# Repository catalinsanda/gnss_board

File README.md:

# gnss_board
Hardware design for the GNSS project

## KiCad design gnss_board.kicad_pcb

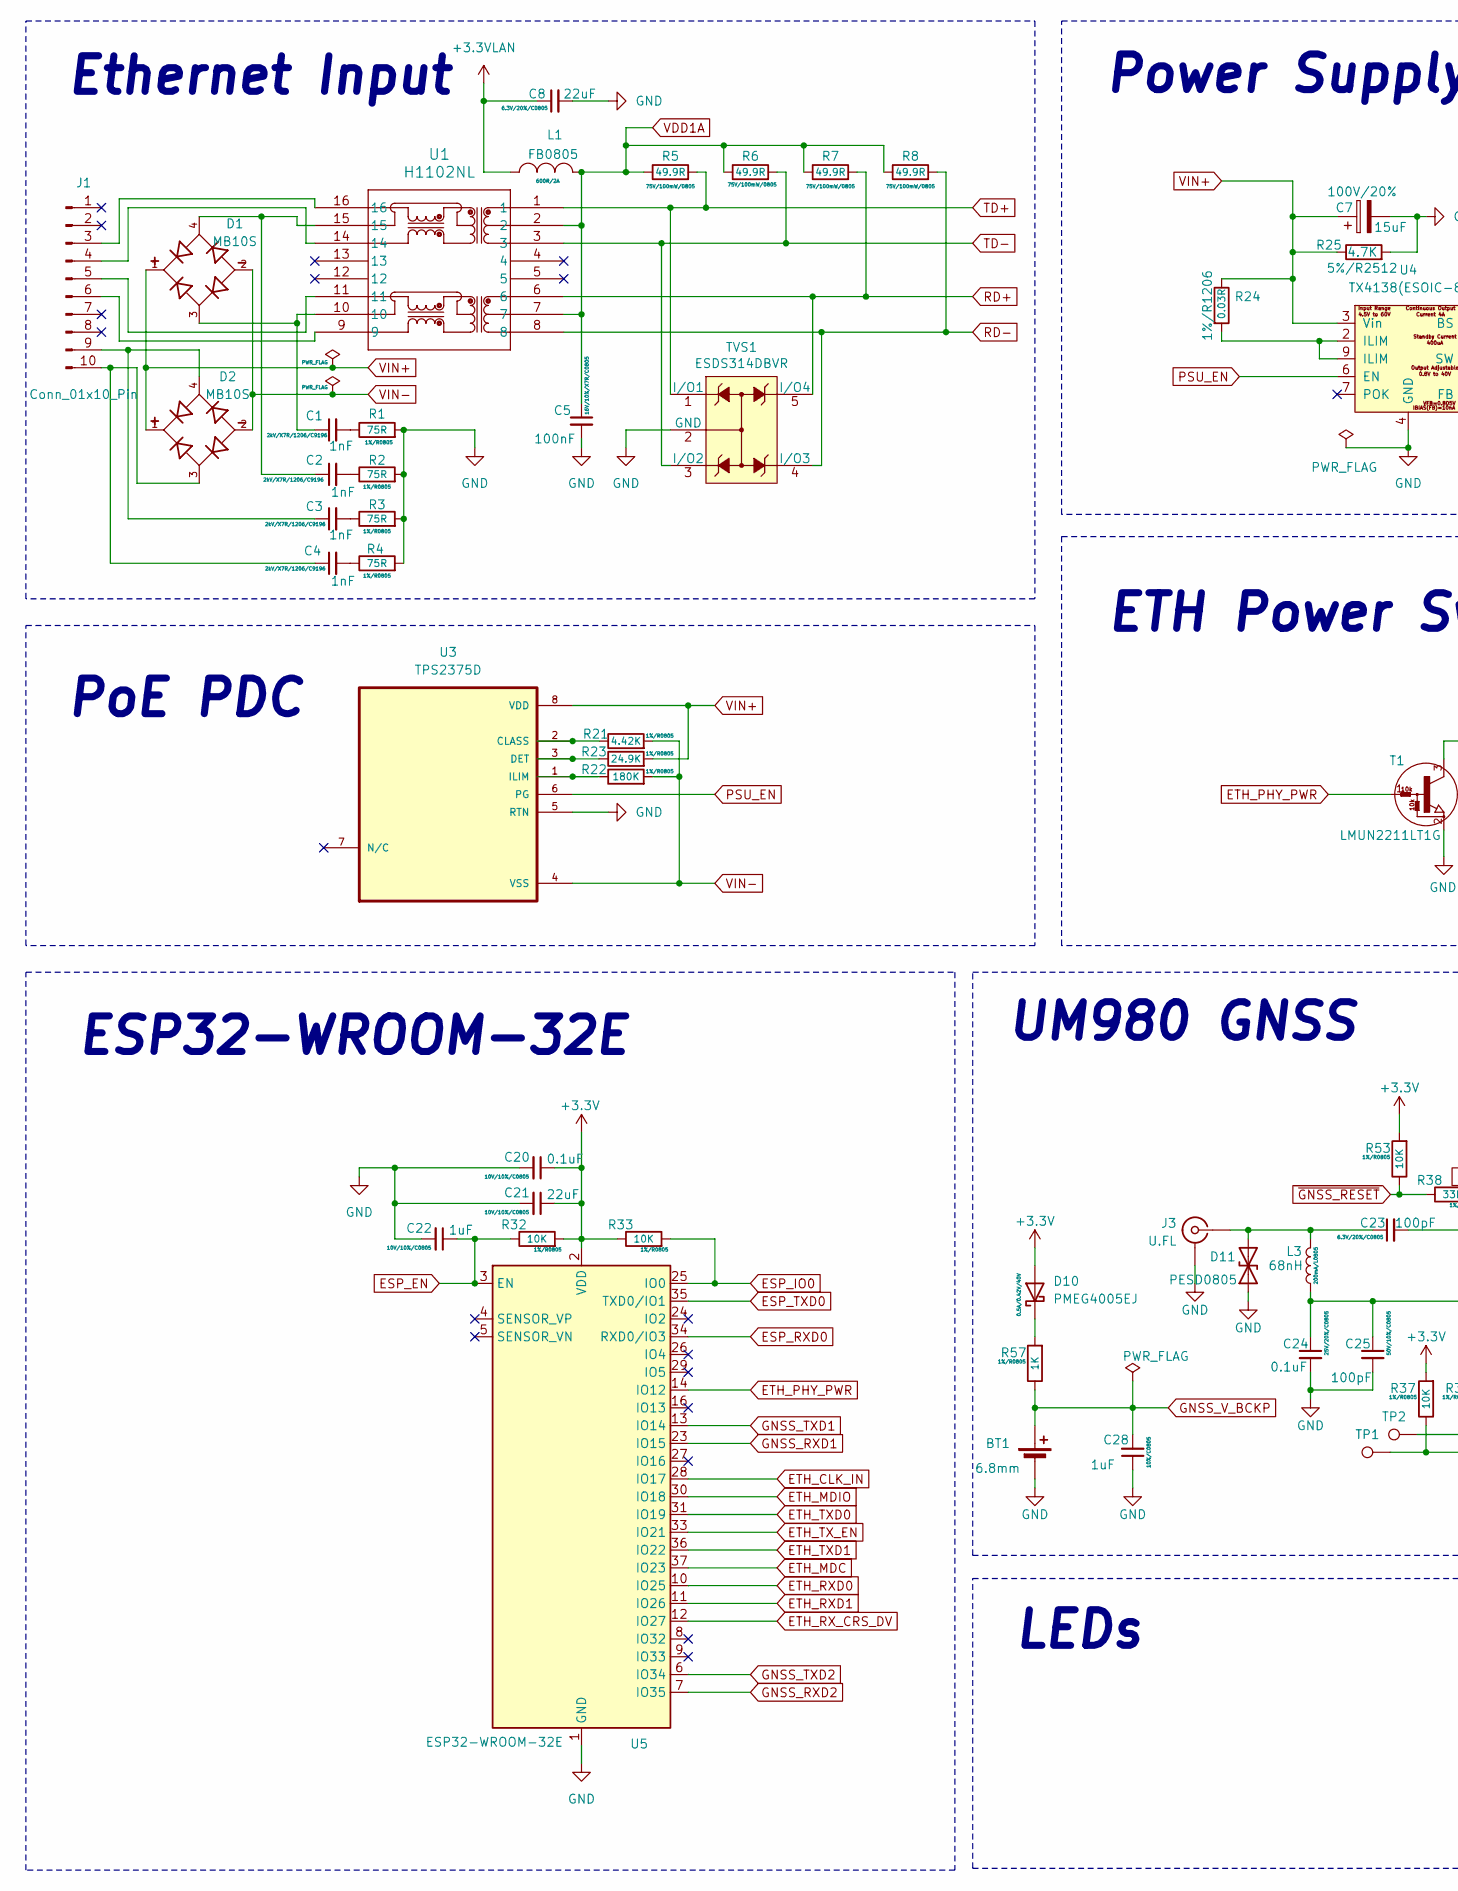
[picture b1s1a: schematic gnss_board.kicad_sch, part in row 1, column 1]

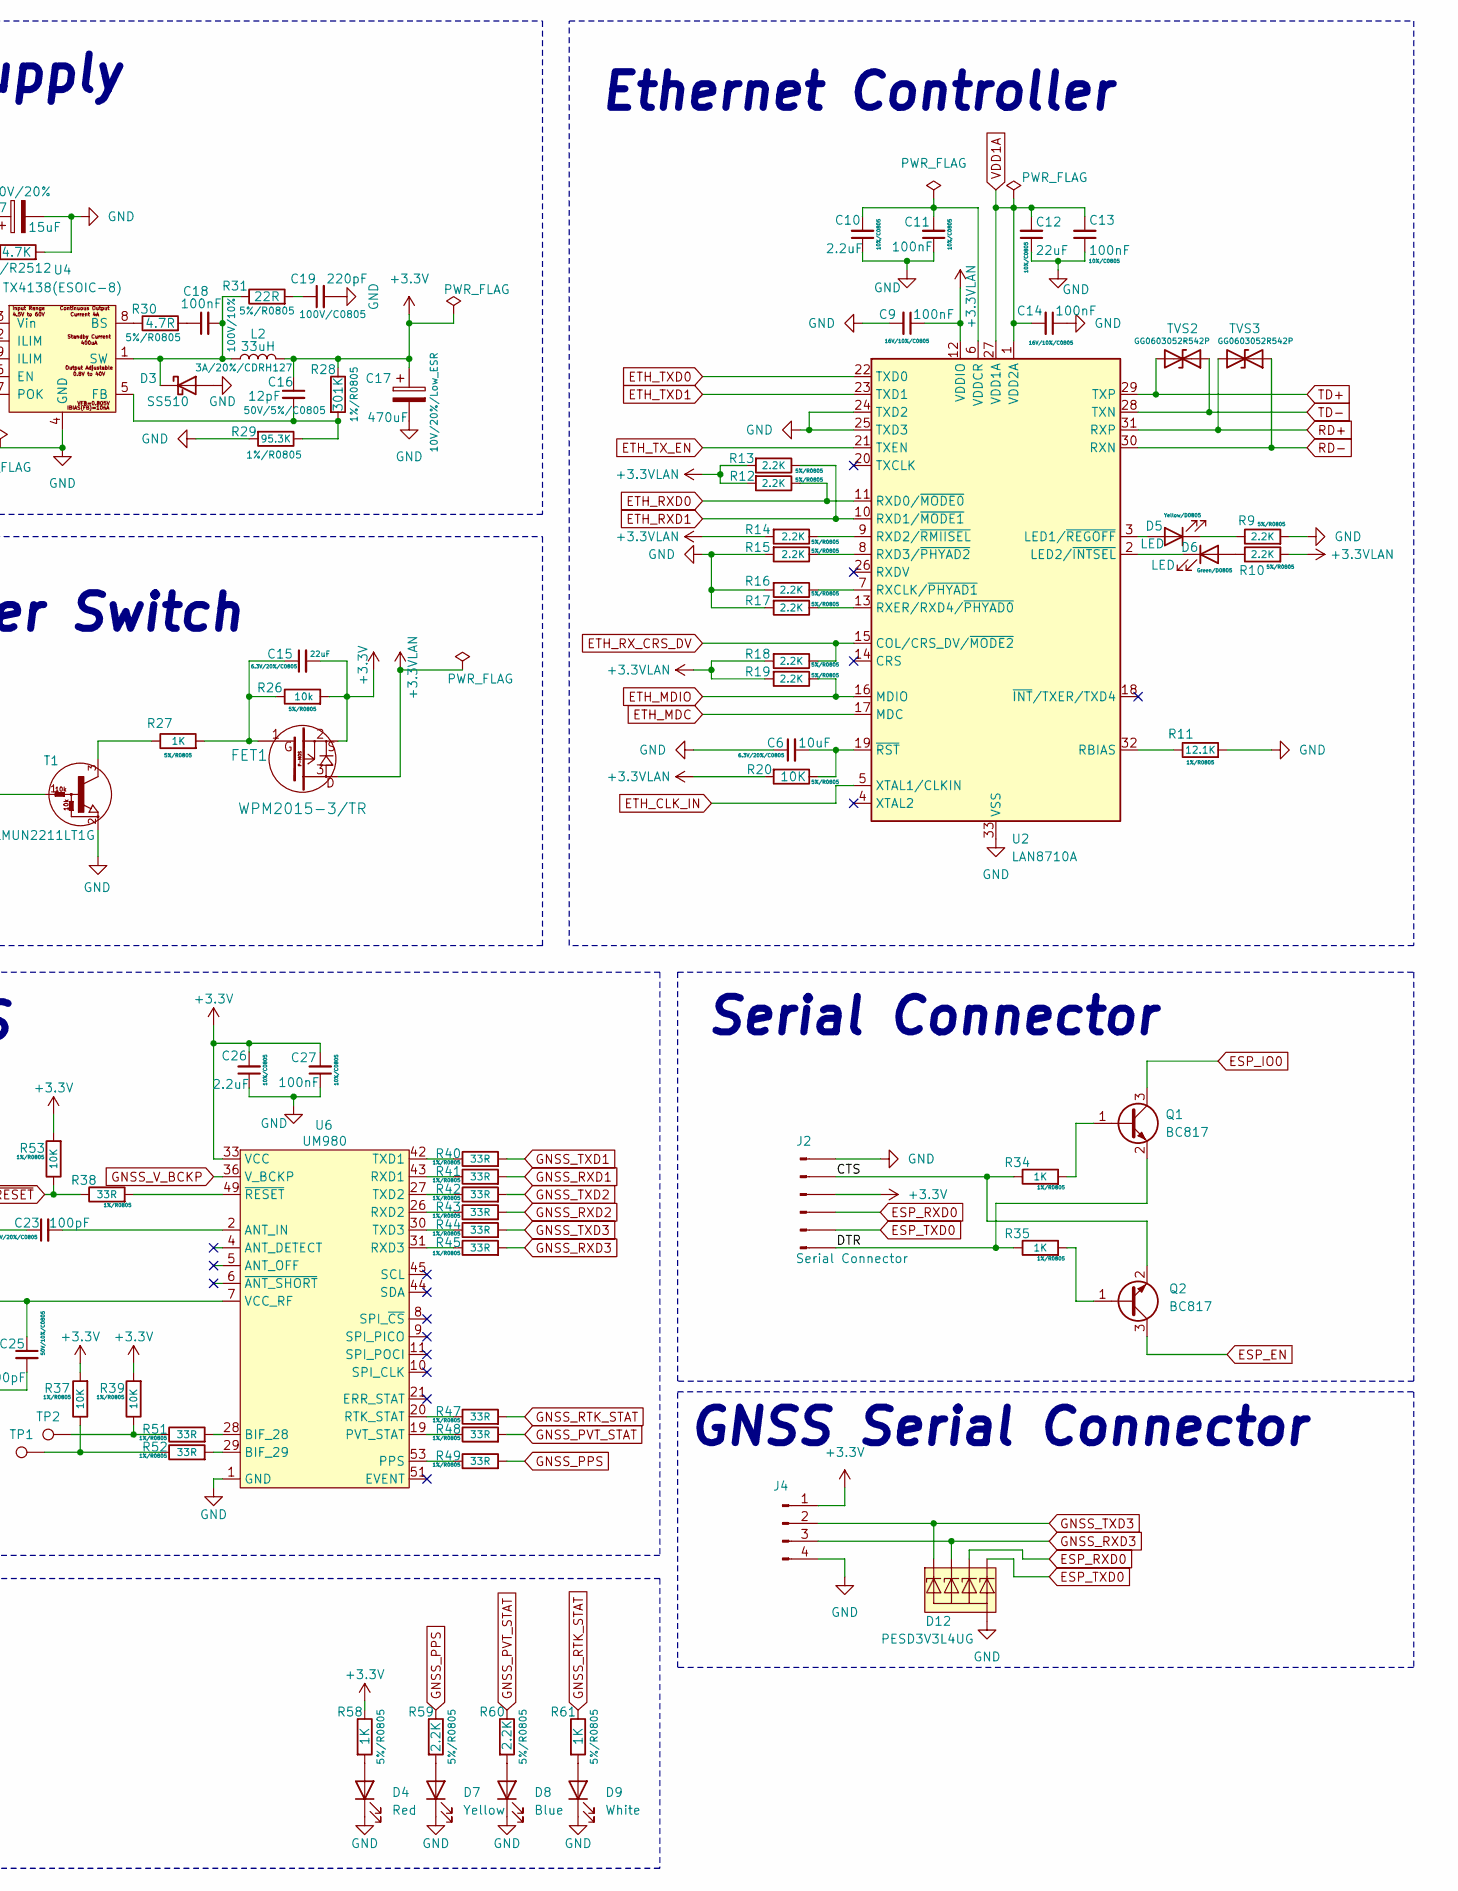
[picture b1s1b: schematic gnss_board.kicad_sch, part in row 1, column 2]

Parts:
BT1: 6.8mm; ML414H_IV01E
C1, C2, C3, C4: 1nF; C_1206_3216Metric
C5, C9, C11, C13, C14, C18, C27: 100nF; C_0805_2012Metric
C6: 10uF; C_0805_2012Metric
C7: 15uF; CP_Radial_D6.3mm_P2.50mm; Part Farnell:1281844
C8, C12, C15, C21: 22uF; C_0805_2012Metric
C10, C26: 2.2uF; C_0805_2012Metric
C16: 12pF; C_0805_2012Metric
C17: 470uF; CP_Radial_D6.3mm_P2.50mm
C19: 220pF; C_0805_2012Metric
C20, C24: 0.1uF; C_0805_2012Metric
C22, C28: 1uF; C_0805_2012Metric
C23, C25: 100pF; C_0805_2012Metric
D1, D2: MB10S; SOIC245P670X290-4N
D3: SS510; D_SMC_Handsoldering
D4: Red; LED_0603_1608Metric_Red
D5, D6: LED; LED_0805_2012Metric
D7: Yellow; LED_0603_1608Metric_Yellow
D8: Blue; LED_0603_1608Metric_Blue
D9: White; LED_0603_1608Metric_White
D10: PMEG4005EJ; SOD-323
D11: PESD0805; C_0805_2012Metric
D12: PESD3V3L4UG; SOT-353_SC-70-5_Handsoldering
FET1: WPM2015-3/TR; SOT-23_Handsoldering
J1: Conn_01x10_Pin; Molex_PicoBlade_53398-1071_1x10-1MP_P1.25mm_Vertical
J2: Serial Connector; PinHeader_1x06_P2.54mm_Vertical
J3: U.FL
J4: Conn_01x04_Pin; PinHeader_1x04_P2.54mm_Vertical
L1: FB0805; L_0805_2012Metric_Pad1.15x1.40mm_HandSolder
L2: 33uH; INDPM120120X800N
L3: 68nH; L_0805_2012Metric_Pad1.05x1.20mm_HandSolder
Q1, Q2: BC817; SOT-23
R1, R2, R3, R4: 75R; R_0805_2012Metric
R5, R6, R7, R8: 49.9R; R_0805_2012Metric
R9, R10, R12, R13, R14, R15, R16, R17, R18, R19, R59, R60: 2.2K; R_0805_2012Metric
R11: 12.1K; R_0805_2012Metric
R20, R32, R33, R37, R39, R53: 10K; R_0805_2012Metric
R21: 4.42K; R_0805_2012Metric
R22: 180K; R_0805_2012Metric
R23: 24.9K; R_0805_2012Metric
R24: 0.03R; R_1206_3216Metric
R25: 4.7K; R_2512_6332Metric
R26: 10k; R_0805_2012Metric
R27, R34, R35, R57, R58, R61: 1K; R_0805_2012Metric
R28: 301K; R_0805_2012Metric
R29: 95.3K; R_0805_2012Metric
R30: 4.7R; R_0805_2012Metric
R31: 22R; R_0805_2012Metric
R38, R40, R41, R42, R43, R44, R45, R47, R48, R49, R51, R52: 33R; R_0805_2012Metric
T1: LMUN2211LT1G; SOT-23_Handsoldering
TP1, TP2: PTH; 1x01
TVS1: ESDS314DBVR; SOT-23-5
TVS2, TVS3: GG0603052R542P; D_0603_1608Metric
U1: H1102NL; H11X_PUL
U2: LAN8710A; QFN-32-1EP_5x5mm_P0.5mm_EP3.3x3.3mm_ThermalVias
U3: TPS2375D; SOIC127P599X175-8N; DigiKey_Part_Number 296-17061-ND
U4: TX4138(ESOIC-8); SOIC-8-1EP_3.9x4.9mm_P1.27mm_EP2.29x3mm_ThermalVias
U5: ESP32-WROOM-32E
U6: UM980

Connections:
+3.3VLAN: C8.1, C9.1, FET1.3, L1.2, R10.2, R12.2, R13.2, R14.2, R18.2, R19.2, R20.2, U2.12 (VDDIO)
/CTS: J2.2, Q2.2 (E), R34.1
/DTR: J2.6, Q1.2 (E), R35.1
/SW: C18.2, D3.1 (K), L2.1, R31.1, U4.1 (SW)
ESP_EN: C22.1, Q2.3 (C), R32.1, U5.3 (EN)
ESP_IO0: Q1.3 (C), R33.2, U5.25 (IO0)
ESP_RXD0: D12.4 (K3), J2.4, U5.34 (RXD0/IO3)
ESP_TXD0: D12.5 (K4), J2.5, U5.35 (TXD0/IO1)
ETH_CLK_IN: U2.5 (XTAL1/CLKIN), U5.28 (IO17)
ETH_MDC: U2.17 (MDC), U5.37 (IO23)
ETH_MDIO: R19.1, U2.16 (MDIO), U5.30 (IO18)
ETH_PHY_PWR: T1.1 (B), U5.14 (IO12)
ETH_RXD0: R12.1, U2.11 (RXD0/~MODE0), U5.10 (IO25)
ETH_RXD1: R13.1, U2.10 (RXD1/~MODE1), U5.11 (IO26)
ETH_RX_CRS_DV: R18.1, U2.15 (COL/CRS_DV/~MODE2), U5.12 (IO27)
ETH_TXD0: U2.22 (TXD0), U5.31 (IO19)
ETH_TXD1: U2.23 (TXD1), U5.36 (IO22)
ETH_TX_EN: U2.21 (TXEN), U5.33 (IO21)
GND: BT1.-, C5.2, C6.1, C7.2, C8.2, C9.2, C10.1, C11.1, C12.1, C13.1, C14.1, C17.2, C19.2, C20.2, C21.2, C22.2, C24.2, C25.2, C26.1, C27.1, C28.1, D3.2 (A), D4.1 (K), D7.1 (K), D8.1 (K), D9.1 (K), D11.1 (A1), D12.2 (A), J2.1, J3.2 (Ext), J4.4, R1.2, R2.2, R3.2, R4.2, R9.2, R11.2, R15.2, R16.2, R17.2, R25.2, R29.2, T1.2 (E), TVS1.2 (GND), U2.24 (TXD2), U2.25 (TXD3), U2.33 (VSS), U3.5 (RTN), U4.4 (GND), U5.1 (GND), U5.15 (GND), U5.38 (GND), U5.39 (GND), U6.1 (GND), U6.3 (GND), U6.12 (GND), U6.14 (GND), U6.32 (GND), U6.37 (GND), U6.41 (GND), U6.48 (GND), U6.55 (GND), U6.56 (GND), U6.57 (GND), U6.58 (GND), U6.59 (GND), U6.60 (GND), U6.61 (GND), U6.62 (GND), U6.63 (GND), U6.64 (GND), U6.65 (GND), U6.66 (GND), U6.67 (GND), U6.68 (GND), U6.69 (GND), U6.70 (GND), U6.71 (GND), U6.72 (GND), U6.73 (GND), U6.74 (GND), U6.75 (GND), U6.76 (GND), U6.77 (GND), U6.78 (GND), U6.79 (GND), U6.80 (GND), U6.81 (GND), U6.82 (GND), U6.83 (GND), U6.84 (GND), U6.85 (GND), U6.86 (GND), U6.87 (GND), U6.88 (GND), U6.89 (GND), U6.90 (GND), U6.91 (GND), U6.92 (GND), U6.93 (GND), U6.94 (GND), U6.95 (GND), U6.96 (GND), U6.97 (GND), U6.98 (GND), U6.99 (GND), U6.100 (GND), U6.101 (GND), U6.102 (GND); also elsewhere on the board
GNSS_PPS: R49.2, R59.1
GNSS_PVT_STAT: R48.2, R60.1
GNSS_RTK_STAT: R47.2, R61.1
GNSS_RXD1: R41.2, U5.23 (IO15)
GNSS_RXD2: R43.2, U5.7 (IO35)
GNSS_RXD3: D12.3 (K2), J4.3, R45.2
GNSS_TXD1: R40.2, U5.13 (IO14)
GNSS_TXD2: R42.2, U5.6 (IO34)
GNSS_TXD3: D12.1 (K1), J4.2, R44.2
GNSS_V_BCKP: BT1.+, C28.2, R57.1, U6.36 (V_BCKP)
unnamed: C1.1, D1.3, U1.10
unnamed: C1.2, R1.1
unnamed: C2.1, D1.4, U1.15
unnamed: C2.2, R2.1
unnamed: C3.2, R3.1
unnamed: C4.2, R4.1
unnamed: C15.1, FET1.1, R26.1, R27.2
unnamed: C18.1, R30.2
unnamed: C19.1, R31.2
unnamed: D4.2 (A), R58.2
unnamed: D5.2 (A), U2.3 (LED1/~REGOFF)
unnamed: D5.1 (K), R9.1
unnamed: D6.2 (A), R10.1
unnamed: D6.1 (K), U2.2 (LED2/~INTSEL)
unnamed: D7.2 (A), R59.2
unnamed: D8.2 (A), R60.2
unnamed: D9.2 (A), R61.2
unnamed: D10.1 (K), R57.2
unnamed: C23.1, D11.2 (A2), J3.1 (In), L3.2
unnamed: J1.3, U1.16
unnamed: J1.4, U1.14
unnamed: J1.5, U1.11
unnamed: J1.6, U1.9
unnamed: C3.1, D2.4, J1.9
unnamed: C4.1, D2.3, J1.10
unnamed: Q1.1 (B), R34.2
unnamed: Q2.1 (B), R35.2
unnamed: R24.2, U4.2 (ILIM), U4.9 (ILIM)
unnamed: R37.1, R52.1, TP1.1
unnamed: R39.1, R51.1, TP2.1
unnamed: R27.1, T1.3 (C)
unnamed: R11.1, U2.32 (RBIAS)
unnamed: R16.1, U2.7 (RXCLK/~PHYAD1)
unnamed: R14.1, U2.9 (RXD2/~RMIISEL)
unnamed: R15.1, U2.8 (RXD3/~PHYAD2)
unnamed: R17.1, U2.13 (RXER/RXD4/~PHYAD0)
unnamed: C10.2, C11.2, U2.6 (VDDCR)
unnamed: C6.2, R20.1, U2.19 (~RST)
unnamed: R21.1, U3.2 (CLASS)
unnamed: R23.1, U3.3 (DET)
unnamed: R22.1, U3.1 (ILIM)
unnamed: R30.1, U4.8 (BS)
unnamed: C16.2, R28.2, R29.1, U4.5 (FB)
unnamed: C23.2, U6.2 (ANT_IN)
unnamed: R51.2, U6.28 (BIF_28)
unnamed: R52.2, U6.29 (BIF_29)
unnamed: R49.1, U6.53 (PPS)
unnamed: R48.1, U6.19 (PVT_STAT)
unnamed: R47.1, U6.20 (RTK_STAT)
unnamed: R41.1, U6.43 (RXD1)
unnamed: R43.1, U6.26 (RXD2)
unnamed: R45.1, U6.31 (RXD3)
unnamed: R40.1, U6.42 (TXD1)
unnamed: R42.1, U6.27 (TXD2)
unnamed: R44.1, U6.30 (TXD3)
unnamed: C24.1, C25.1, L3.1, U6.7 (VCC_RF)
unnamed: R38.2, U6.49 (~RESET)
PSU_EN: U3.6 (PG), U4.6 (EN)
RD+: R7.2, TVS1.5 (I/O4), TVS3.2 (A2), U1.6, U2.31 (RXP)
RD-: R8.2, TVS1.4 (I/O3), TVS3.1 (A1), U1.8, U2.30 (RXN)
TD+: R5.2, TVS1.1 (I/O1), TVS2.2 (A2), U1.1, U2.29 (TXP)
TD-: R6.2, TVS1.3 (I/O2), TVS2.1 (A1), U1.3, U2.28 (TXN)
VDD1A: C5.1, C12.2, C13.2, C14.2, L1.1, R5.1, R6.1, R7.1, R8.1, U1.2, U1.7, U2.1 (VDD2A), U2.27 (VDD1A)
VIN+: C7.1, D1.1, D2.1, R23.2, R24.1, R25.1, U3.8 (VDD), U4.3 (Vin)
VIN-: D1.2, D2.2, R21.2, R22.2, U3.4 (VSS)
~GNSS_RESET: R38.1, R53.1

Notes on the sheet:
GNSS Serial Connector
ETH Power Switch
Power Supply
PoE PDC
Ethernet Input
Serial Connector
LEDs
Ethernet Controller
ESP32-WROOM-32E
UM980 GNSS

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
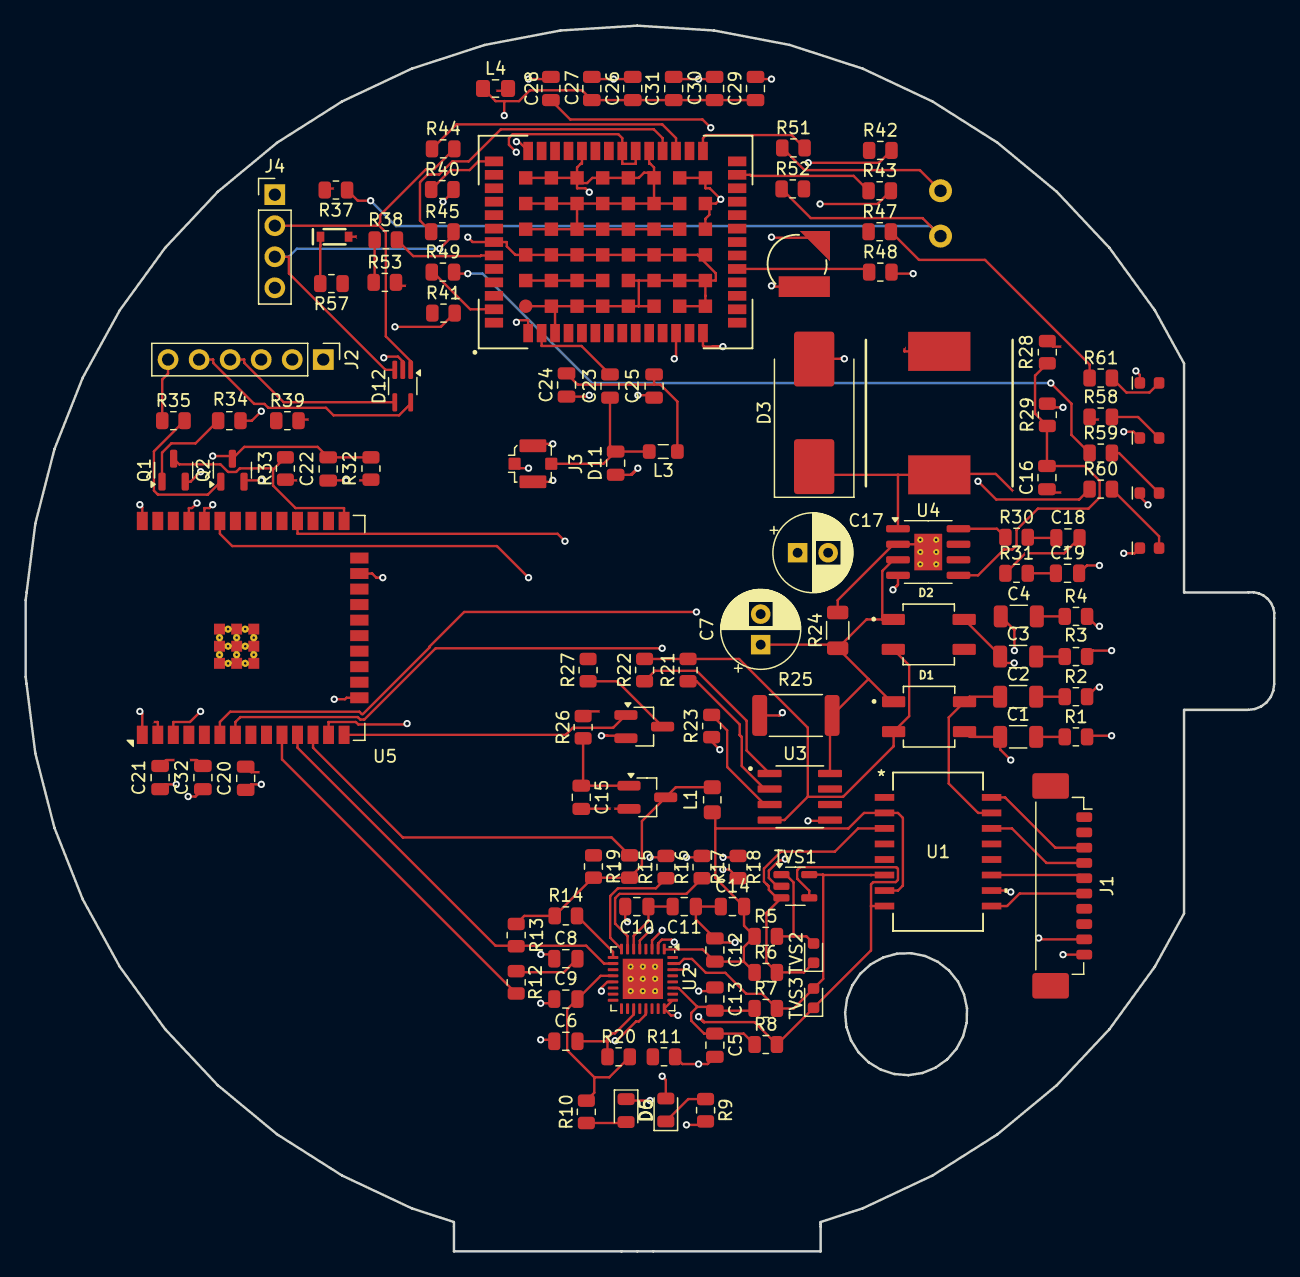
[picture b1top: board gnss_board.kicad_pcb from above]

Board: 4 copper layers, 102.2 x 100.3 mm, 123 parts (0 on the bottom side), 97 nets.

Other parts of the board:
C29, C30, C31: 10uF; C_0805_2012Metric
C32: 22uF; C_0805_2012Metric
L4: FB0805; L_0805_2012Metric_Pad1.15x1.40mm_HandSolder

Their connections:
GND: C29.1, C30.1, C31.1, C32.2; also elsewhere on the board

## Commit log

2025-03-23 Initial commit - just for backup
2025-03-24 Schematic of the power supply with footprings
2025-03-28 Slowly grinding
2025-03-30 Add footprints and arange components around
2025-03-30 Update connector
2025-04-04 Add power supply to ESP32
2025-04-05 Connect ESP32 to the LAN chip
2025-04-07 Add Serial Connector for programming
2025-04-14 Add SparkFun Symbols & Footprints
2025-04-18 Add GNSS module as well
2025-04-18 PCB Edges
2025-04-19 Messing around
2025-04-20 Moving components around
2025-04-22 All components have been added
2025-04-22 Playing around with the auto-router
2025-04-22 Let's add this as well
2025-04-24 Update prints
2025-04-24 Update project
